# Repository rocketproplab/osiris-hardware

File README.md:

# osiris-hardware: Team Workflow Guide

This repo holds all Osiris KiCad projects. Read this once before touching anything. It covers: what git actually is, one-time setup, the daily workflow, and the rules that keep us from destroying each other's work.

---

## 1. What git is (2 minutes, skip if you know)

Git tracks every version of every file, forever. GitHub is the website where our shared copy lives.

Four words you'll see constantly:

- **Clone**: download the repo to your computer. You do this once.
- **Branch**: a personal workspace. Think of `main` as the master document everyone trusts, and a branch as your own scratch copy. You make changes on your branch; `main` stays untouched until your work is approved.
- **Commit**: a saved checkpoint of your changes, with a message describing what you did. Like hitting save, but with a note attached.
- **Merge (via Pull Request)**: asking for your branch's changes to be folded into `main`. On GitHub this is called a Pull Request (PR). Someone reviews it, approves it, and clicks merge. That's the only way changes reach `main`.

You never edit `main` directly. The repo is configured to block it.

## 2. One-time setup

### Install
1. Install git: https://git-scm.com/downloads (Mac users: it may already be installed, check with `git --version` in Terminal)
2. Install KiCad 10: https://www.kicad.org/download/
3. Make a GitHub account and get added to the rocketproplab org (ask Edgar).

### Clone the repo
Open a terminal and run:

```bash
git clone https://github.com/rocketproplab/osiris-hardware.git
cd osiris-hardware
```

### Point KiCad at our shared library (do this BEFORE opening any project)
Order matters here. KiCad only auto-substitutes the path variable into libraries added after the variable exists.

1. Open KiCad. Go to **Preferences → Configure Paths**.
2. Click **+** and add:
   - Name: `RPL_LIB`
   - Path: the full path to the `lib` folder inside your cloned repo (e.g. `/Users/you/osiris-hardware/lib`)
3. Click OK.

That's it. Board projects in this repo reference the team library through `${RPL_LIB}`, so they'll open correctly on your machine now.

### Tell git who you are (first time only)
```bash
git config --global user.name "Your Name"
git config --global user.email "you@ucsd.edu"
```

## 3. The daily workflow (the only 6 commands you need)

Every piece of work follows the same loop. No exceptions.

```bash
# 1. Get the latest version of main
git checkout main
git pull

# 2. Make your personal workspace (name it after the work)
git checkout -b feature/lsm6dsox-footprint

# 3. Do your work in KiCad. Save your files.

# 4. Checkpoint your work
git add -A
git commit -m "Add LSM6DSOX footprint and 3D model"

# 5. Upload your branch to GitHub
git push -u origin feature/lsm6dsox-footprint

# 6. Open a Pull Request
# Go to the repo on github.com. A yellow banner will offer
# "Compare & pull request". Click it, describe what you did, submit.
```

After someone approves and merges your PR, your work is in `main`. Delete the branch (GitHub offers a button) and start the loop again for your next task.

**If you're ever confused about what state you're in:** run `git status`. It tells you what branch you're on and what's changed. When in doubt, ask before running commands you don't understand. Nothing in git is truly lost, but untangling takes time.

## 4. Repo layout

```
osiris-hardware/
  lib/                    THE SHARED TEAM LIBRARY
    symbols/              rpl.kicad_sym (schematic symbols)
    footprints/rpl.pretty/  (PCB footprints)
    3dmodels/rpl.3dshapes/  (3D models)
  boards/                 ONE FOLDER PER BOARD
    demo-board/
  fab/                    empty on purpose, see Releases below
```

## 5. The two kinds of work, and the rules for each

### Library work: symbols, footprints, 3D models. OPEN TO EVERYONE.
This is where most people contribute, especially at first. It's safe parallel work because you're adding new parts, not editing shared board files.

Rules:
- Every symbol must have two fields filled in: **MPN** (manufacturer part number) and **Datasheet** (a link). No exceptions. A part without a datasheet link doesn't get merged.
- Before making a part, check it doesn't already exist in the library.
- One part (or one related set of parts) per branch/PR. Small PRs get reviewed fast.

### Board work: schematics and PCB layout. ONE OWNER AT A TIME.
KiCad board files cannot be merged. If two people edit the same `.kicad_pcb`, one person's work gets thrown away. So:

- Each folder in `boards/` has exactly one owner at a time.
- If you don't own the board, don't touch its folder. Feed the owner footprints through library PRs instead.
- Ownership is announced in the team channel and handed off explicitly.

## 6. Things that will bite you if ignored

- **Always pull before branching.** Skipping step 1 means you're building on stale files, and your PR will conflict.
- **Never commit to main.** It's blocked, but don't try.
- **Don't commit generated junk.** The `.gitignore` handles backups, autosaves, and `.kicad_prl` (per-user view settings). If git shows changes to files you didn't knowingly edit, ask before committing.
- **Fab outputs (gerbers) never go in the repo.** When a board is sent to fab, the owner generates gerbers, zips them, and attaches the zip to a GitHub Release with a tag like `demo-board-revA`. That tag is our permanent record of exactly what was manufactured.

## 7. Cheat sheet

| I want to... | Command |
|---|---|
| See what state I'm in | `git status` |
| Get latest main | `git checkout main` then `git pull` |
| Start new work | `git checkout -b feature/short-name` |
| Save a checkpoint | `git add -A` then `git commit -m "message"` |
| Upload my branch | `git push -u origin feature/short-name` |
| Get my work into main | Open a Pull Request on github.com |

Questions: ask in the AV channel. Asking early beats untangling later.

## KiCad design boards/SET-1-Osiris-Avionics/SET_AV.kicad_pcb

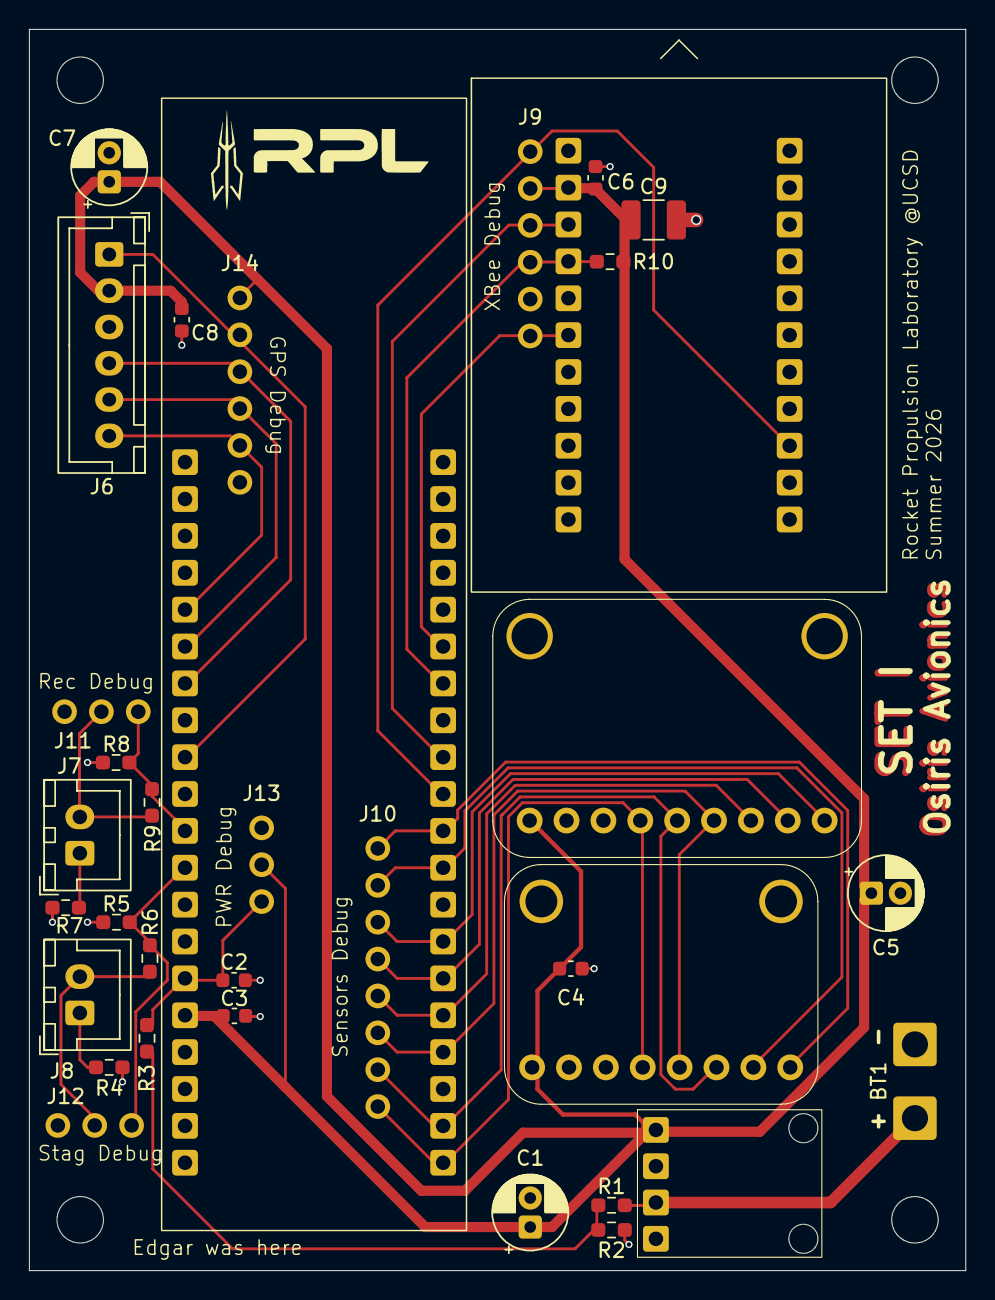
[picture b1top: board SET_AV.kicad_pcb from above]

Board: 2 copper layers, 64.5 x 85.5 mm, 34 parts (0 on the bottom side), 27 nets.

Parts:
BT1: Battery; battery_pads
C1, C5, C7: 47uF; CP_Radial_D5.0mm_P2.00mm
C2, C3, C4, C6, C8: 100nF; C_0603_1608Metric
C9: 100uF; C_1210_3225Metric_Pad1.33x2.70mm_HandSolder
J1: ESP32P4ETH (socket); Waveshare_ESP32-P4-ETH
J2: AP63203 Buck (socket); SparkFun_BabyBuck_AP63203
J3: BMP388 (socket); Adafruit_BMP388
J4: LSM6DSOX (socket); Adafruit_LSM6DSOX
J5: XBee PRO S3B (socket); SparkFun_XBee_PRO_S3B_USB
J6: Adafruit PA1616D JST-XH header (male); JST_XH_B6B-XH-A_1x06_P2.50mm_Vertical
J7: BR recovery signal; JST_XH_B2B-XH-A_1x02_P2.50mm_Vertical
J8: BR staging signal; JST_XH_B2B-XH-A_1x02_P2.50mm_Vertical
J9: XBee Debug; 6-pin-debug
J10: Sensor Debug; PinHeader_1x08_P2.54mm_Vertical
J11: Recovery Debug; PinHeader_1x03_P2.54mm_Vertical
J12: Staging Debug; PinHeader_1x03_P2.54mm_Vertical
J13: Battery Debug; PinHeader_1x03_P2.54mm_Vertical
J14: GPS Debug; 6-pin-debug
R1: 6.8k; R_0603_1608Metric_Pad0.98x0.95mm_HandSolder
R2: 2.7k; R_0603_1608Metric_Pad0.98x0.95mm_HandSolder
R3, R4, R7: 1k; R_0603_1608Metric_Pad0.98x0.95mm_HandSolder
R5, R8: 3.6k; R_0603_1608Metric_Pad0.98x0.95mm_HandSolder
R6, R9: 4.7k; R_0603_1608Metric_Pad0.98x0.95mm_HandSolder
R10: 10k; R_0603_1608Metric_Pad0.98x0.95mm_HandSolder

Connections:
/3V3: C1.1, C3.2, C4.1, C5.1, C6.2, C7.1, C8.1, C9.1, J1.36 (3V3), J2.1 (3V3), J3.1 (VIN), J4.1 (VIN), J5.2 (3.3V), J6.2 (Vin), J9.2, J13.2, J14.1, R10.1
/Net-(J1-4): J1.14 (3), J5.4 (DIN), J9.4, R10.2
GND: BT1.2 (-), C1.2, C2.1, C3.1, C4.2, C5.2, C6.1, C7.2, C8.2, C9.2, J1.3 (GND), J1.8 (GND), J1.13 (GND), J1.18 (GND), J1.23 (GND), J1.28 (GND), J1.33 (GND), J1.38 (GND), J2.2 (GND), J3.3 (GND), J4.3 (GND), J5.1 (GND), J5.11 (GND), J6.3 (GND), J9.5, J11.3, J12.3, J13.1, J14.6, R2.1, R4.1, R5.2, R7.2, R8.2
unnamed: BT1.1 (+), J2.3 (VIN), R1.2
unnamed: J1.15 (2), J5.6 (RST), J9.6
unnamed: J1.12 (4), J5.3 (DOUT), J9.3
unnamed: J1.11 (5), J5.14 (CTS), J9.1
unnamed: J1.10 (6), J3.8 (INT), J10.1
unnamed: J1.9 (14), J3.7 (CS), J10.2
unnamed: J1.7 (15), J4.9 (I2), J10.3
unnamed: J1.6 (16), J4.8 (I1), J10.4
unnamed: J1.5 (17), J4.7 (CS), J10.5
unnamed: J1.4 (18), J3.5 (SDO), J4.6 (DO), J10.6
unnamed: J1.2 (19), J3.6 (SDA), J4.5 (SDA), J10.7
unnamed: C2.2, J1.35 (20), J13.3, R3.1
unnamed: J1.32 (22), J12.1, R5.1, R6.2
unnamed: J1.31 (23), J11.1, R8.1, R9.2
unnamed: J1.29 (26), J6.1 (PPS), J14.2
unnamed: J1.26 (32), J6.5 (TX), J14.4
unnamed: J1.25 (33), J6.6 (EN), J14.5
unnamed: J1.1 (54), J3.4 (SCL), J4.4 (SCL), J10.8
unnamed: J7.1, R7.1
unnamed: J8.1, R4.2
unnamed: J7.2, J11.2, R9.1
unnamed: J8.2, J12.2, R6.1
unnamed: J1.27, J6.4 (RX), J14.3
unnamed: R1.1, R2.2, R3.2
